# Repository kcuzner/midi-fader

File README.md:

# Simple MIDI Fader

By Kevin Cuzner

## Project Status

 * PCB complete and working (with an additional load added to reduce regulator noise)
 * Firmware feature-complete and mostly working
   * Emulates as HID and USB-MIDI devices
   * Not tested on Windows yet
 * Case OpenSCAD in progress
 * Configuration host software in progress

## Featureset

 * Two 60mm analog fader inputs
 * USB Audio Class interface, aiming for driverless on Windows 7 and 10
 * Driverless HID interface for configuration
   * It might be trivially simple to echo the fader status in the HID reports...

## Main Component Options

 * Faders (note that they have different footprints and different levers):
   * Expensive faders ($4.74, very light movement force): PTB6053-2010APB103-ND
   * Cheap faders ($1.73): PTA6043-2015CPB103-ND
 * Microcontrollers:
   * 497-17354-1-ND: STM32F070F6P6, $1.48, 32K flash, 6K RAM, 20-TSSOP.
     * No CRS, external XTAL required.
   * 497-15099-ND: STM32F070CBT6, $2.52, 128K flash, 16K RAM, 48-LQFP
     * No CRS, exteranl XTAL required.
   * 497-17344-ND: STM32042F6P6, $2.25, 32K flash, 6K RAM, 20-TSSOP.
     * Has a CRS
     * 24.6mA with all peripherals and HSI48 enabled
 * 609-4052-1-ND: Micro-USB, $0.76
 * 455-1790-1-ND: JST-SH header for programming, $0.63
 * Power supply solution:
   * MCP1603T-330I/OSCT-ND: Cheap buck regulator, but not too cheap. $1.01,
     TSOT-23
     * Noise issues at low currents (leaves PWM mode and skips pulses).
   * 576-4764-1-ND: MIC5504 buck regulator, $0.11, SOT23-5.
     * At a 100mA load, the case will heat 42.6C. Not over the top, but really
       quite hot.
     * We could do this AND the buck regulator, but just have this for the
       analog.

## Notes

### Notes about the logical MIDI protocol

 * MIDI has two types of bytes STATUS and DATA.
 * A STATUS byte has its MSB set
 * A DATA byte has its MSB cleared (hence why there are only ever 0 to 127 data
   values)
 * Usually, the lower nybble of the STATUS byte is a channel number (there are
   16 channels).
 * The number of data bytes to follow varies by which STATUS byte preceded them.
 * Interesting STATUS commands (upper nybble shown) for this project:
   * 0xB: Control Change. Followed by a controller number (1 data byte) and a
     controller value (1 data byte). Although there are possibly 127 controller
     numbers, numbers 120-127 are reserved for "Channel Mode Messages". Several
     of these are commonly used.
   * 0xE: Pitch Bend. Followed by two DATA bytes encoding a 14-bit value, LSB
     first. 0x2000 is center.
 * https://www.cs.cmu.edu/~music/cmsip/readings/MIDI%20tutorial%20for%20programmers.html
 * https://www.midi.org/specifications-old/item/table-1-summary-of-midi-message

### Notes about USB and MIDI

 * Windows XP and above seem to support USB MIDI except Elements.
   * "Elements" are things that process MIDI
   * "Jacks" are supported, and they are exactly what they sound like. This will
     implement a Jack.
   * Elements and Jacks are "Entities"
 * http://www.usb.org/developers/docs/devclass_docs/midi10.pdf

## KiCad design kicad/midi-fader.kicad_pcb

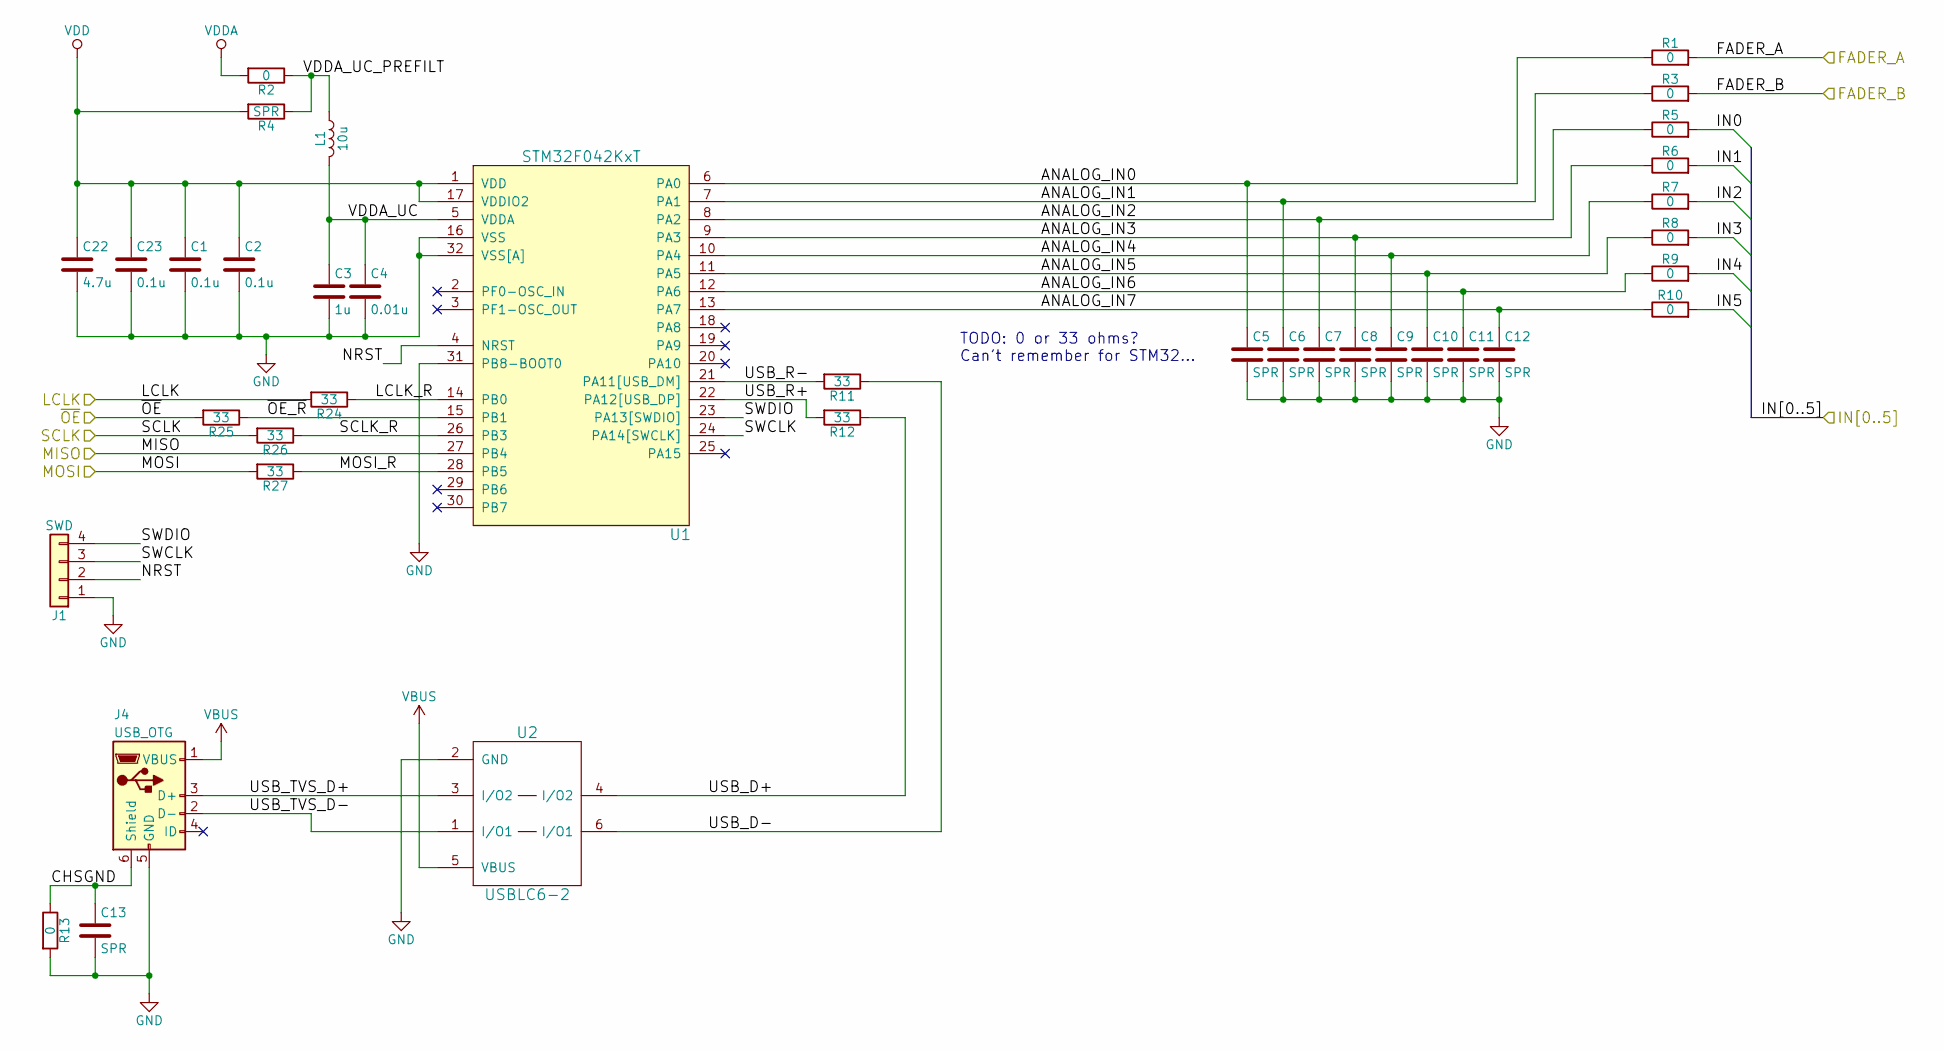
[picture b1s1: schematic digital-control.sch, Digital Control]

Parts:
C1, C2, C23: 0.1u; C_0402; Part No. 1276-1043-1-ND
C3: 1u; C_0603; Part No. 1276-1182-1-ND
C4: 0.01u; C_0402; Part No. 399-1038-1-ND
C5, C6, C7, C8, C9, C10, C11, C12, C13: SPR; C_0402
C22: 4.7u; C_0805; Part No. 1276-6464-1-ND
J1: SWD; JST-SH-4; Part No. 455-1790-1-ND
J4: USB_OTG; AMP-10104110-USB; Part No. 609-4052-1-ND
L1: 10u; R_0805; Part No. 587-2045-1-ND
R1, R2, R3, R5, R6, R7, R8, R9, R10, R13: 0; R_0402
R4: SPR; R_0402
R11, R12, R24, R25, R26, R27: 33; R_0402
U1: STM32F042KxT; LQFP-32_7x7mm_Pitch0.8mm; Part No. 497-14647-ND
U2: USBLC6-2; SOT-666; Part No. 497-5026-1-ND

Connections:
/Digital Control/ANALOG_IN0: C5.1, R1.1, U1.6 (PA0)
/Digital Control/ANALOG_IN1: C6.1, R3.1, U1.7 (PA1)
/Digital Control/ANALOG_IN2: C7.1, R5.1, U1.8 (PA2)
/Digital Control/ANALOG_IN3: C8.1, R6.1, U1.9 (PA3)
/Digital Control/ANALOG_IN4: C9.1, R7.1, U1.10 (PA4)
/Digital Control/ANALOG_IN5: C10.1, R8.1, U1.11 (PA5)
/Digital Control/ANALOG_IN6: C11.1, R9.1, U1.12 (PA6)
/Digital Control/ANALOG_IN7: C12.1, R10.1, U1.13 (PA7)
/Digital Control/CHSGND: C13.1, J4.6 (Shield), R13.1
/Digital Control/FADER_A: R1.2; also elsewhere on the board
/Digital Control/FADER_B: R3.2; also elsewhere on the board
/Digital Control/IN0: R5.2; also elsewhere on the board
/Digital Control/IN1: R6.2; also elsewhere on the board
/Digital Control/IN2: R7.2; also elsewhere on the board
/Digital Control/IN3: R8.2; also elsewhere on the board
/Digital Control/IN4: R9.2; also elsewhere on the board
/Digital Control/IN5: R10.2; also elsewhere on the board
/Digital Control/LCLK: R24.2; also elsewhere on the board
/Digital Control/LCLK_R: R24.1, U1.14 (PB0)
/Digital Control/MISO: U1.27 (PB4); also elsewhere on the board
/Digital Control/MOSI: R27.2; also elsewhere on the board
/Digital Control/MOSI_R: R27.1, U1.28 (PB5)
/Digital Control/NRST: J1.2, U1.4 (NRST)
/Digital Control/SCLK: R26.2; also elsewhere on the board
/Digital Control/SCLK_R: R26.1, U1.26 (PB3)
/Digital Control/SWCLK: J1.3, U1.24 (PA14[SWCLK])
/Digital Control/SWDIO: J1.4, U1.23 (PA13[SWDIO])
/Digital Control/USB_D+: R12.1, U2.4 (I/O2)
/Digital Control/USB_D-: R11.1, U2.6 (I/O1)
/Digital Control/USB_R+: R12.2, U1.22 (PA12[USB_DP])
/Digital Control/USB_R-: R11.2, U1.21 (PA11[USB_DM])
/Digital Control/USB_TVS_D+: J4.3 (D+), U2.3 (I/O2)
/Digital Control/USB_TVS_D-: J4.2 (D-), U2.1 (I/O1)
/Digital Control/VDDA_UC: C3.1, C4.1, L1.2, U1.5 (VDDA)
/Digital Control/VDDA_UC_PREFILT: L1.1, R2.1, R4.1
/Digital Control/~OE: R25.2; also elsewhere on the board
/Digital Control/~OE_R: R25.1, U1.15 (PB1)
GND: C1.2, C2.2, C3.2, C4.2, C5.2, C6.2, C7.2, C8.2, C9.2, C10.2, C11.2, C12.2, C13.2, C22.2, C23.2, J1.1, J4.5 (GND), R13.2, U1.16 (VSS), U1.31 (PB8-BOOT0), U1.32 (VSS[A]), U2.2 (GND); also elsewhere on the board
VBUS: J4.1 (VBUS), U2.5 (VBUS); also elsewhere on the board
VDD: C1.1, C2.1, C22.1, C23.1, R4.2, U1.1 (VDD), U1.17 (VDDIO2); also elsewhere on the board
VDDA: R2.2; also elsewhere on the board

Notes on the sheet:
TODO: 0 or 33 ohms? Can't remember for STM32...

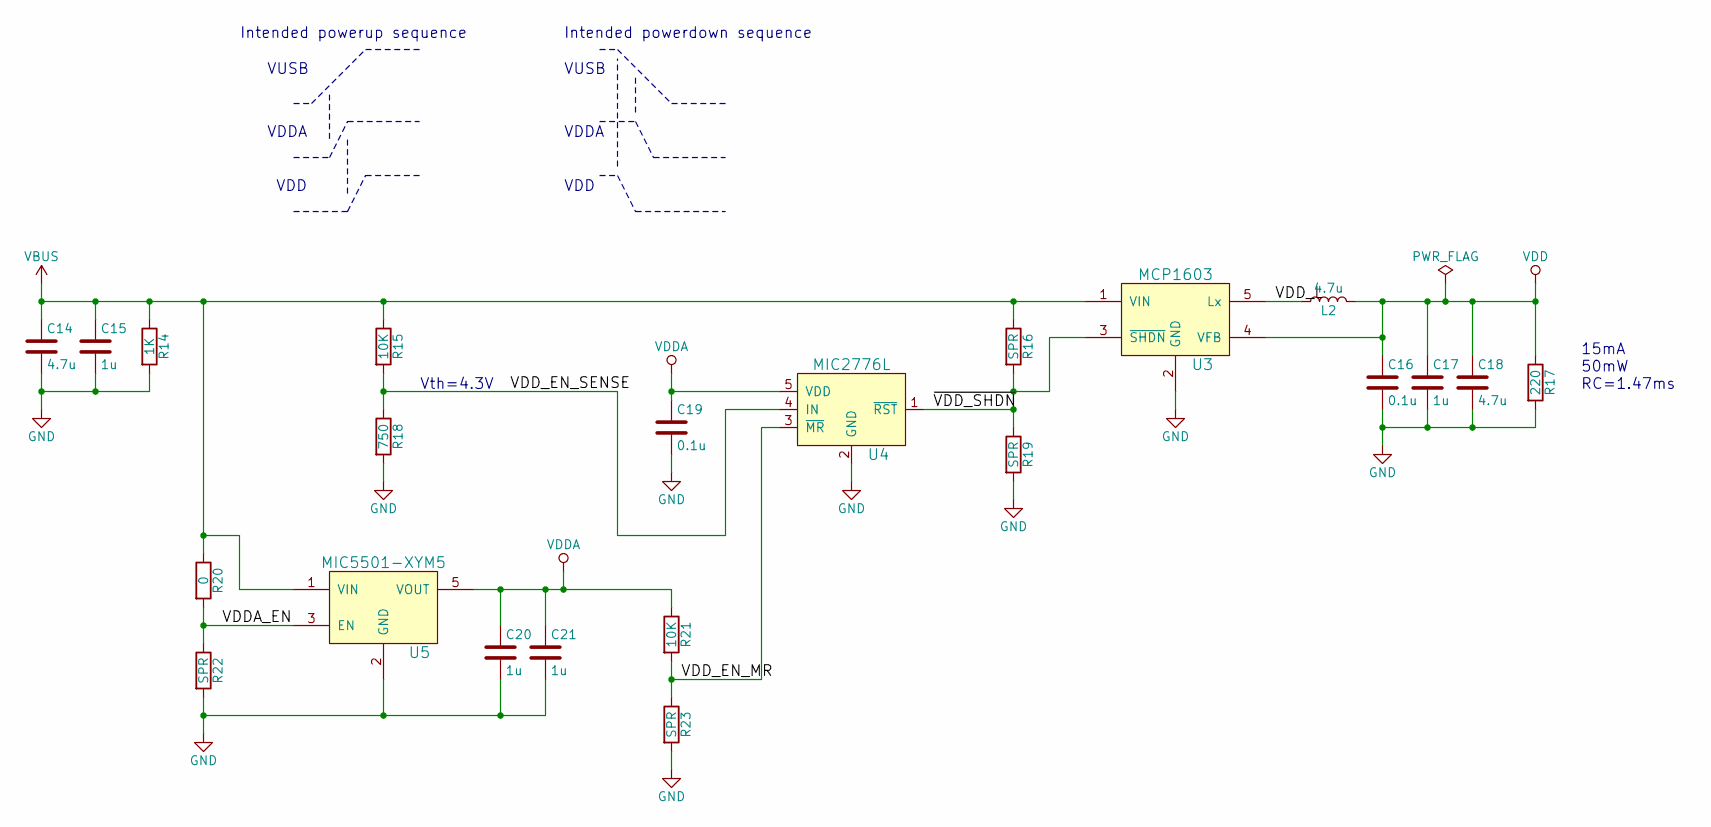
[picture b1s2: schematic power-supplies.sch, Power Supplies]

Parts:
C14, C18: 4.7u; C_0805; Part No. 1276-6464-1-ND
C15, C17, C20, C21: 1u; C_0603; Part No. 1276-1182-1-ND
C16, C19: 0.1u; C_0402; Part No. 1276-1043-1-ND
L2: 4.7u; Wurth_TPC_3816; Part No. 732-1008-1-ND
R14: 1K; R_0805
R15, R21: 10K; R_0402
R16, R19, R22, R23: SPR; R_0402
R17: 220; R_1206
R18: 750; R_0402
R20: 0; R_0402
U3: MCP1603; TSOT-23-5; Part No. MCP1603T-330I/OSCT-ND
U4: MIC2776L; SOT-23-5; Part No. 576-2686-1-ND
U5: MIC5501-XYM5; SOT-23-5; Part No. 576-4764-1-ND

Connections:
/Power Supplies/VDDA_EN: R20.2, R22.1, U5.3 (EN)
/Power Supplies/VDD_EN_MR: R21.2, R23.1, U4.3 (~MR)
/Power Supplies/VDD_EN_SENSE: R15.2, R18.1, U4.4 (IN)
/Power Supplies/VDD_L: L2.1, U3.5 (Lx)
/Power Supplies/~VDD_SHDN: R16.2, R19.1, U3.3 (~SHDN), U4.1 (~RST)
GND: C14.2, C15.2, C16.2, C17.2, C18.2, C19.2, C20.2, C21.2, R14.2, R17.2, R18.2, R19.2, R22.2, R23.2, U3.2 (GND), U4.2 (GND), U5.2 (GND); also elsewhere on the board
VBUS: C14.1, C15.1, R14.1, R15.1, R16.1, R20.1, U3.1 (VIN), U5.1 (VIN); also elsewhere on the board
VDD: C16.1, C17.1, C18.1, L2.2, R17.1, U3.4 (VFB); also elsewhere on the board
VDDA: C19.1, C20.1, C21.1, R21.1, U4.5 (VDD), U5.5 (VOUT); also elsewhere on the board

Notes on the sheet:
Intended powerup sequence
VUSB
VDDA
VDD
Intended powerdown sequence
15mA 50mW RC=1.47ms
Vth=4.3V

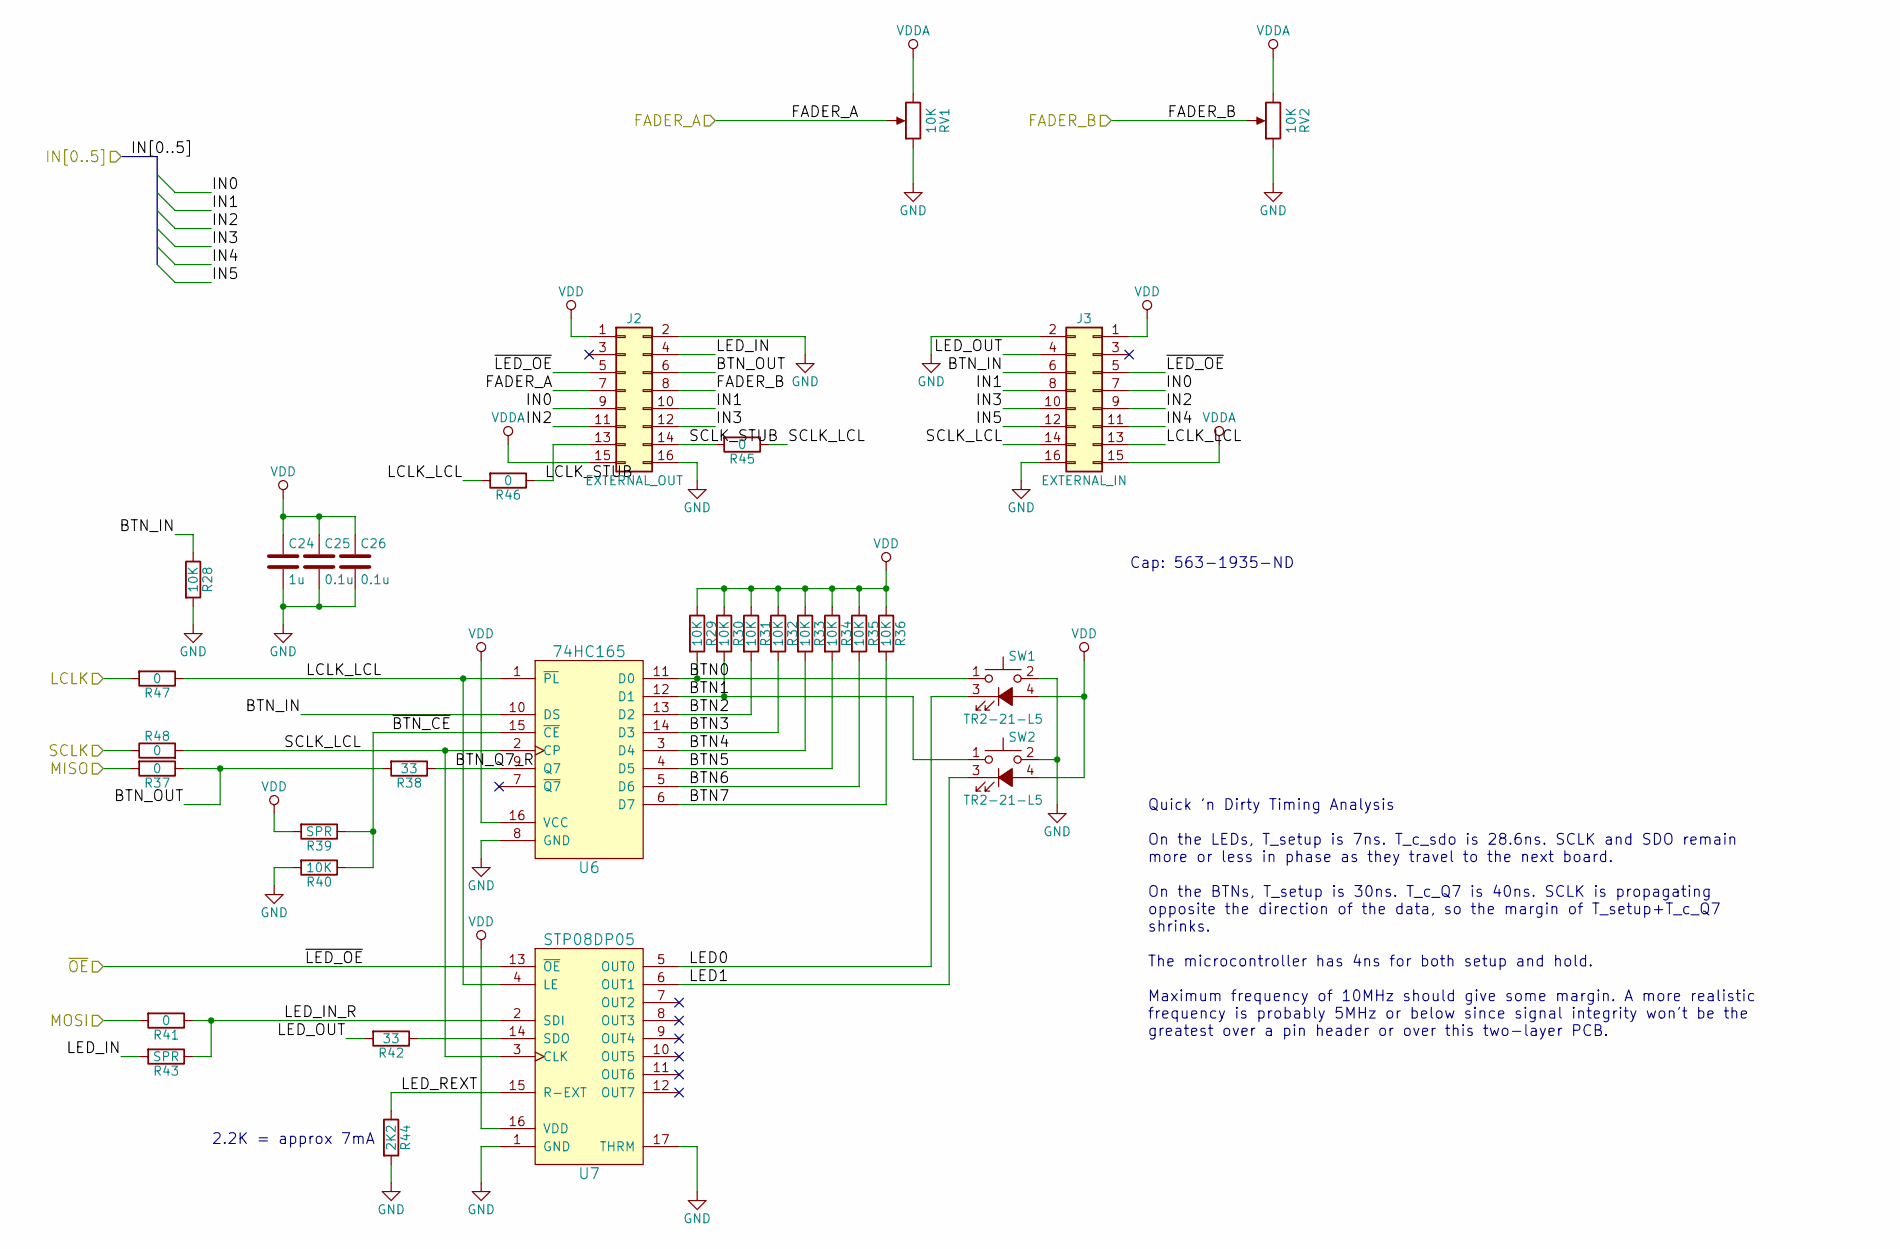
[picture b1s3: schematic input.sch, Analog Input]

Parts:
C24: 1u; C_0603; Part No. 1276-1182-1-ND
C25, C26: 0.1u; C_0402; Part No. 1276-1043-1-ND
J2: EXTERNAL_OUT; Pin_Header_Angled_2x08_Pitch2.54mm; Part No. 609-3346-ND
J3: EXTERNAL_IN; Socket_Strip_Angled_2x08_Pitch2.54mm; Part No. S5561-ND
R28, R29, R30, R31, R32, R33, R34, R35, R36, R40: 10K; R_0402
R37, R41, R45, R46, R47, R48: 0; R_0402
R38, R42: 33; R_0402
R39, R43: SPR; R_0402
R44: 2K2; R_0402
RV1, RV2: 10K; BOURNS_PTA60X3; Part No. PTA6043-2015CPB103-ND
SW1, SW2: TR2-21-L5; Nidec_Copal_TR2; Part No. 563-1933-ND
U6: 74HC165; TSSOP-16_4.4x5mm_Pitch0.65mm; Part No. 1727-4295-1-ND
U7: STP08DP05; HTSSOP-16-1EP_4.4x5mm_Pitch0.65mm_ThermalVias_HandSolder; Part No. 497-6119-1-ND

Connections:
/Digital Control/FADER_A: J2.7, RV1.2; also elsewhere on the board
/Digital Control/FADER_B: J2.8, RV2.2; also elsewhere on the board
/Digital Control/IN0: J2.9, J3.7; also elsewhere on the board
/Digital Control/IN1: J2.10, J3.8; also elsewhere on the board
/Digital Control/IN2: J2.11, J3.9; also elsewhere on the board
/Digital Control/IN3: J2.12, J3.10; also elsewhere on the board
/Digital Control/IN4: J3.11; also elsewhere on the board
/Digital Control/IN5: J3.12; also elsewhere on the board
/Digital Control/LCLK: R47.2; also elsewhere on the board
/Digital Control/MISO: R37.2; also elsewhere on the board
/Digital Control/MOSI: R41.2; also elsewhere on the board
/Digital Control/SCLK: R48.1; also elsewhere on the board
/Digital Control/~OE: J2.5, J3.5, U7.13 (~OE); also elsewhere on the board
/Input/BTN0: R29.2, SW1.1, U6.11 (D0)
/Input/BTN1: R30.2, SW2.1, U6.12 (D1)
/Input/BTN2: R31.2, U6.13 (D2)
/Input/BTN3: R32.2, U6.14 (D3)
/Input/BTN4: R33.2, U6.3 (D4)
/Input/BTN5: R34.2, U6.4 (D5)
/Input/BTN6: R35.2, U6.5 (D6)
/Input/BTN7: R36.2, U6.6 (D7)
/Input/BTN_IN: J3.6, R28.1, U6.10 (DS)
/Input/BTN_OUT: J2.6, R37.1, R38.2
/Input/BTN_Q7_R: R38.1, U6.9 (Q7)
/Input/LCLK_LCL: J3.13, R46.2, R47.1, U6.1 (~PL), U7.4 (LE)
/Input/LCLK_STUB: J2.13, R46.1
/Input/LED0: SW1.3 (K), U7.5 (OUT0)
/Input/LED1: SW2.3 (K), U7.6 (OUT1)
/Input/LED_IN: J2.4, R43.2
/Input/LED_IN_R: R41.1, R43.1, U7.2 (SDI)
/Input/LED_OUT: J3.4, R42.2
/Input/LED_REXT: R44.1, U7.15 (R-EXT)
/Input/SCLK_LCL: J3.14, R45.1, R48.2, U6.2 (CP), U7.3 (CLK)
/Input/SCLK_STUB: J2.14, R45.2
/Input/~BTN_CE: R39.1, R40.1, U6.15 (~CE)
GND: C24.2, C25.2, C26.2, J2.2, J2.16, J3.2, J3.16, R28.2, R40.2, R44.2, RV1.1, RV2.1, SW1.2, SW2.2, U6.8 (GND), U7.1 (GND), U7.17 (THRM); also elsewhere on the board
unnamed: R42.1, U7.14 (SDO)
VDD: C24.1, C25.1, C26.1, J2.1, J3.1, R29.1, R30.1, R31.1, R32.1, R33.1, R34.1, R35.1, R36.1, R39.2, SW1.4 (A), SW2.4 (A), U6.16 (VCC), U7.16 (VDD); also elsewhere on the board
VDDA: J2.15, J3.15, RV1.3, RV2.3; also elsewhere on the board

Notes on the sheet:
2.2K = approx 7mA
Quick 'n Dirty Timing Analysis On the LEDs, T_setup is 7ns. T_c_sdo is 28.6ns. SCLK and SDO remain more or less in phase as they travel to the next board. On the BTNs, T_setup is 30ns. T_c_Q7 is 40ns. SCLK is propagating opposite the direction of the data, so the margin of T_setup+T_c_Q7 shrinks. T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
Cap: 563-1935-ND

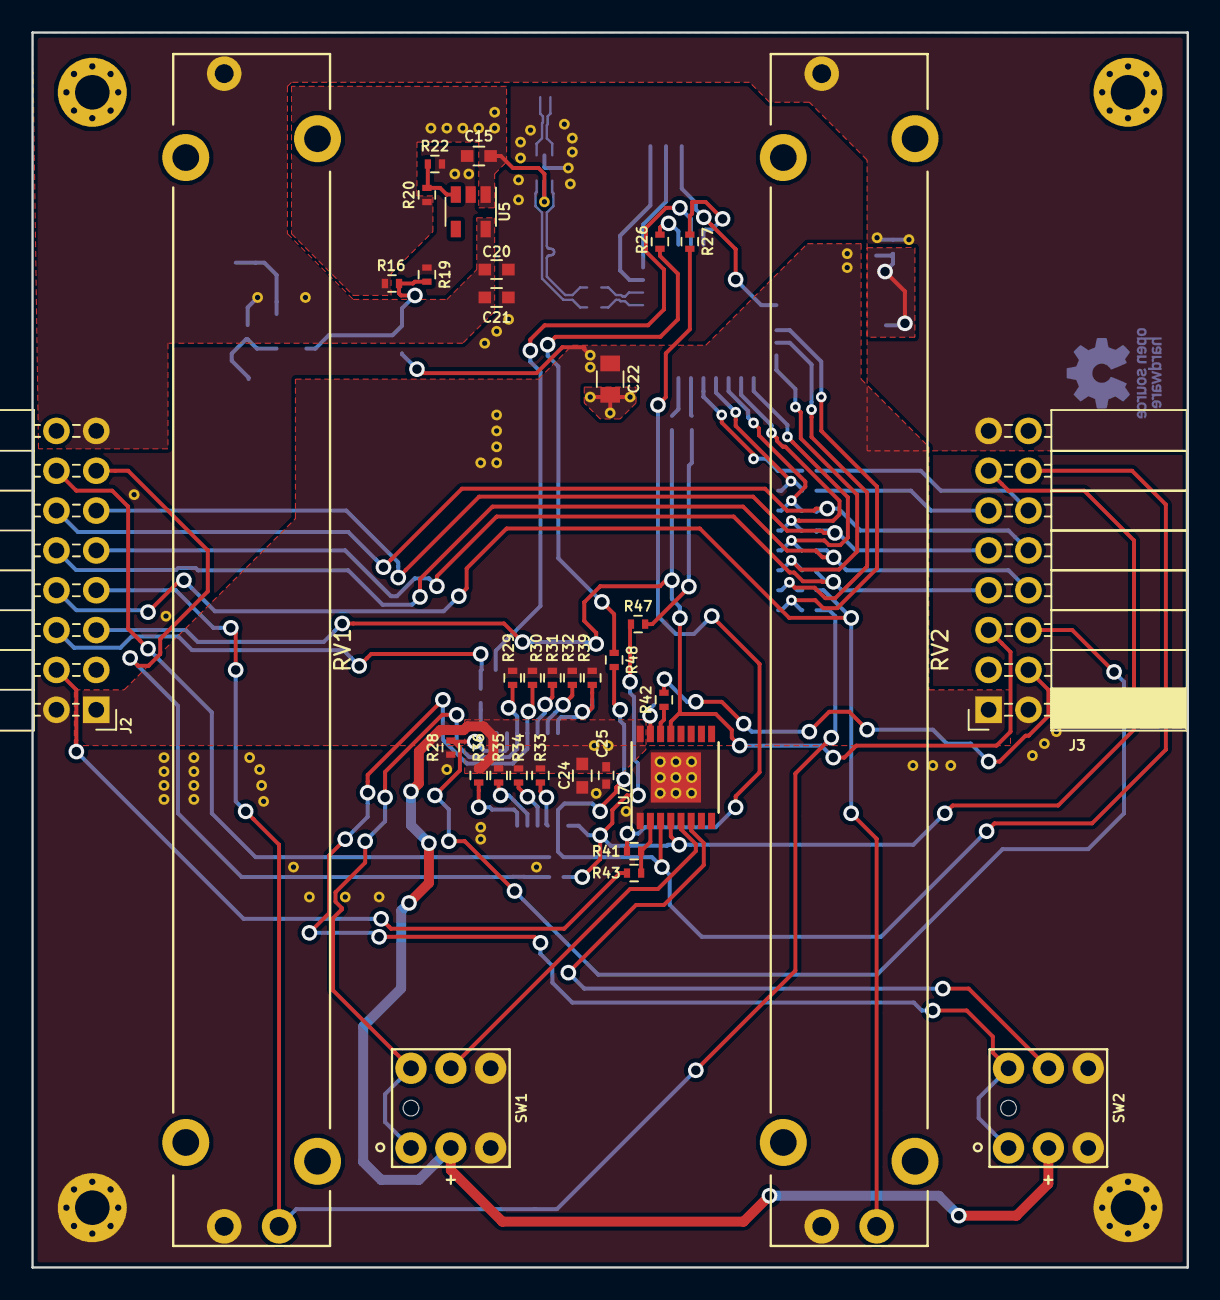
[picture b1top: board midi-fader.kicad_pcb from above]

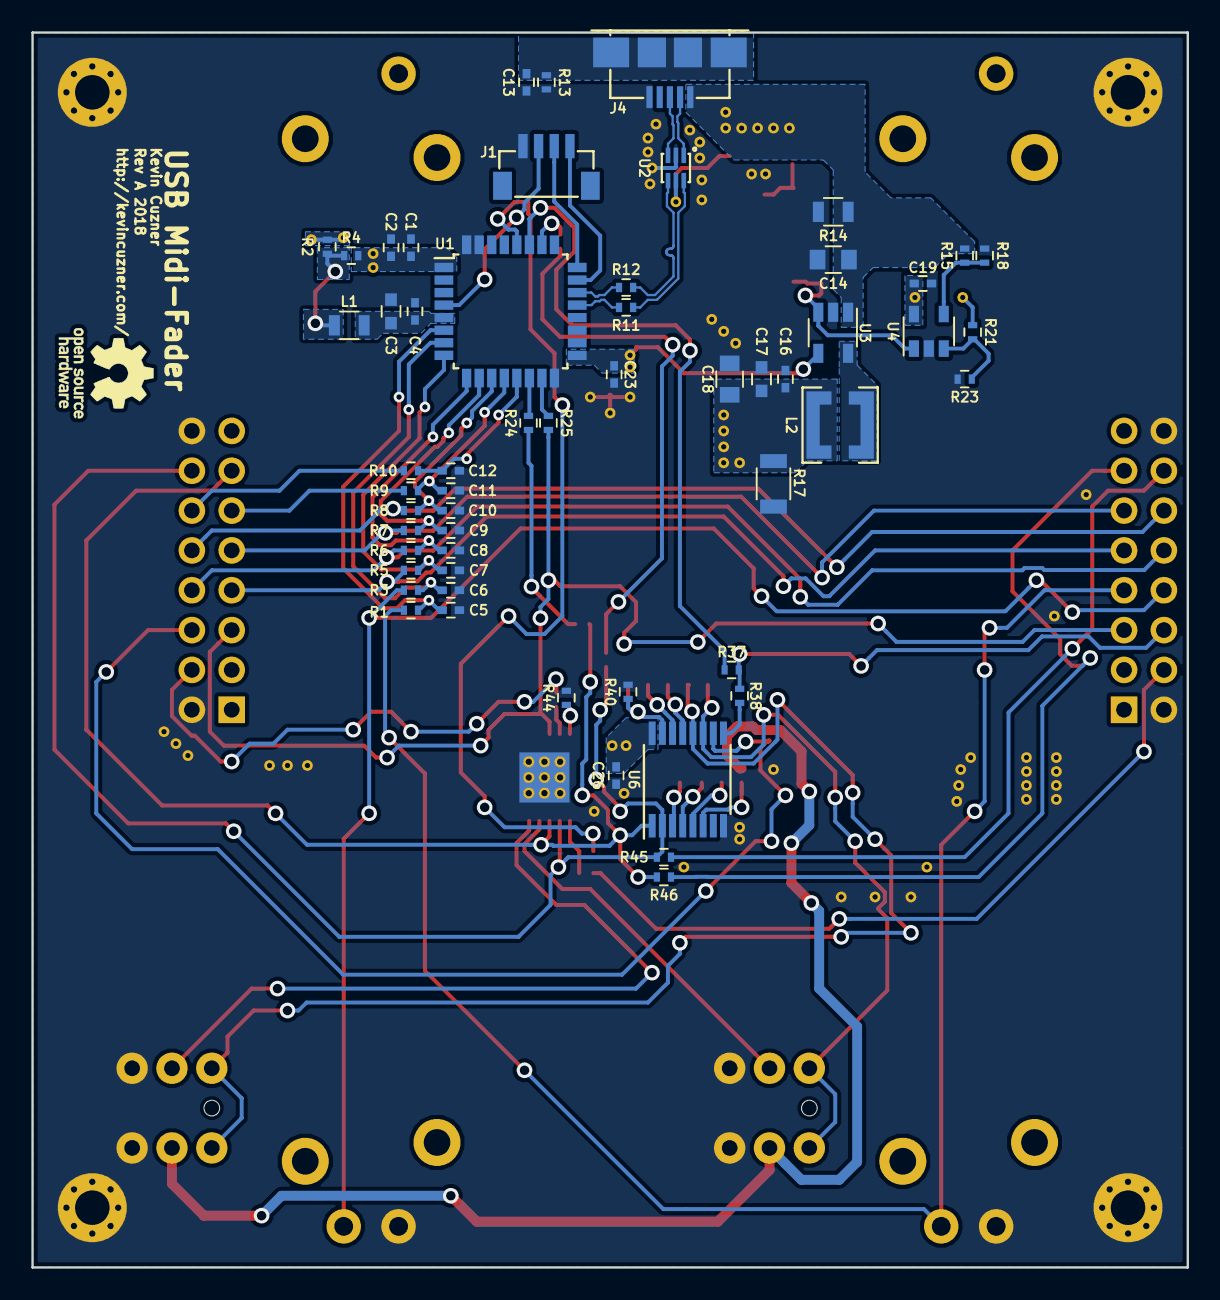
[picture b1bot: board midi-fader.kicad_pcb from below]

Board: 2 copper layers, 73.7 x 78.7 mm, 91 parts (56 on the bottom side), 69 nets.

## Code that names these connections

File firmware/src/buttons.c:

/**
 * USB Midi-Fader
 *
 * Buttons and LEDs
 *
 * Kevin Cuzner
 */

#include "buttons.h"

#include "stm32f0xx.h"
#include "systick.h"

/**
 * This uses the SPI peripheral to operate the shift registers that attach to
 * the buttons and LEDs on each midi-fader board.
 *
 * There can be up to four shift register pairs attached to one controller
 * board. The last shift register pair is noted by being all zeros when no
 * buttons are pressed. The number of channels in the system is determined by
 * how many of those bytes are non-zero. This number can grow and shrink
 * dynamically, even though we don't explicitly support hot-plugging of the
 * additional fader modules (in fact, I think it might cause weird behavior in
 * this module when they are being plugged in).
 */

/**
 * Receive buffer for the button status
 *
 * Buttons are clocked MSB first, so the 1st byte is this board and the last
 * byte is the farthest board.
 */
static volatile uint8_t buttons_status[4];
/**
 * Transmit buffer for the LED status
 *
 * LEDs are clocked MSB first, so the last byte is this board and the 1st byte
 * is the farthest board (opposite the buttons).
 */
static volatile uint8_t leds_status[4];

/**
 * Flag set to true when a transfer is ongoing
 */
static uint8_t transfer_ongoing = 0;

/**
 * Begins a DMA-driven transfer on the SPI if one isn't already ongoing.
 *
 * The DMA channel must be configured in advance
 *
 * This method should not be called reentrantly..
 */
static void buttons_begin_transfer(void)
{
    if (transfer_ongoing)
        return;
    // this variable is only set to 1 inside this method, which is not called
    // reentrantly.
    transfer_ongoing = 1;

    // Workaround for bad wiring: De-assert OE#, bring LCLK high.
    //
    // This allows the input shift register to give us good data, at the
    // expense of the LED register outputting everything as it sees it come
    // in from the master (hence deasserting OE#). To counteract the dimming
    // effect, the transfer is only initiated periodically rather than right
    // after the previous one finishes.
    //
    // Note that OE will be latched by the LEDs on the falling edge of the
    // first clock cycle, even though LCLK will be latched on the rising edge.
    GPIOB->BSRR = GPIO_BSRR_BS_0 | GPIO_BSRR_BS_1;

    // Set up the DMA transfer sizes
    DMA1_Channel2->CNDTR = sizeof(buttons_status);
    DMA1_Channel3->CNDTR = sizeof(leds_status);

    // See section 25.8.9 in the reference manual for this procedure
    // Step 1: Enable RX DMAEN
    SPI1->CR2 |= SPI_CR2_RXDMAEN;
    // Step 2: Enable DMA Streams
    DMA1_Channel2->CCR |= DMA_CCR_EN;
    DMA1_Channel3->CCR |= DMA_CCR_EN;
    // Step 3: Enable TX DMAEN
    SPI1->CR2 |= SPI_CR2_TXDMAEN;
    // Step 4: Start the transfer
    SPI1->CR1 |= SPI_CR1_SPE;
}

/**
 * Concludes a DMA-driven transfer on the SPI
 *
 * This should only be called once the receive transfer (DMA_Channel3)
 * is completed.
 *
 * Also pulses the LCLK both to prepare the buttons for the next transfer
 * and to display the LED values from this transfer
 *
 * This method should not be called reentrantly.
 */
static void buttons_end_transfer(void)
{
    // See section 25.8.9 in the reference manual for this procedure
    // Step 1: Disable the DMA streams
    DMA1_Channel3->CCR &= ~DMA_CCR_EN;
    // Step 2: Follow the SPI disable procedure
    // Step 2.1: Wait for the transmit fifo to be empty
    while (SPI1->SR & SPI_SR_FTLVL_Msk) { }
    // Step 2.2: Wait for busy to clear
    while (SPI1->SR & SPI_SR_BSY) { }
    // Step 2.3: Disable the SPI
    SPI1->CR1 &= ~SPI_CR1_SPE;
    // Step 2.4: Wait for the receive buffer to clear
    while (SPI1->SR & SPI_SR_FRLVL_Msk) { }
    //TODO: I suspect that I should keep RX enabled until this point, just in case
    DMA1_Channel2->CCR &= ~DMA_CCR_EN;
    // Step 3: Clear the DMAEN bits
    SPI1->CR2 &= ~(SPI_CR2_RXDMAEN | SPI_CR2_TXDMAEN);

    // Workaround for bad wiring: Assert OE#, bring LCLK low.
    //
    // This is the reverse of the workaround during the begin transfer phase.
    // It also latches the next batch of data.
    GPIOB->BSRR = GPIO_BSRR_BR_0 | GPIO_BSRR_BR_1;

    // Perform one extra clock cycle.
    //
    // The rising edge latches LCLK and the falling edge latches OE#.
    //
    // Hopefully this doesn't wreak to much havoc with the buttons. The PL#
    // input is asynchronous and it is deasserted just before the first clock
    // cycle the next transaction, so the buttons *should* have the most
    // recent value. Everything looks right when tested with only one shift
    // register, so I don't know if this actually works.
    GPIOB->BSRR = GPIO_BSRR_BR_3;
    GPIOB->MODER ^= GPIO_MODER_MODER3_1 | GPIO_MODER_MODER3_0;
    GPIOB->BSRR = GPIO_BSRR_BS_3;
    GPIOB->BSRR = GPIO_BSRR_BR_3;
    GPIOB->MODER ^= GPIO_MODER_MODER3_1 | GPIO_MODER_MODER3_0;

    // This is only reset in this one place, and this is not called reentrantly.
    transfer_ongoing = 0;
}

void buttons_init(void)
{
    // Enable SPI and GPIOB
    RCC->APB2ENR |= RCC_APB2ENR_SPI1EN;
    RCC->AHBENR |= RCC_AHBENR_GPIOBEN;

    // Enable DMA
    RCC->AHBENR |= RCC_AHBENR_DMA1EN;

    // PB0, PB1, PB3, PB4, and PB5 are the button/led pins
    GPIOB->MODER &= ~(GPIO_MODER_MODER0_Msk | GPIO_MODER_MODER1_Msk |
            GPIO_MODER_MODER3_Msk | GPIO_MODER_MODER4_Msk |
            GPIO_MODER_MODER5_Msk);

    // Configure latch clock and OE pins
    //
    // LCLK: PB0 (starts low)
    // OE#: PB1 (starts high)
    GPIOB->BSRR = GPIO_BSRR_BR_0 | GPIO_BSRR_BS_1;
    GPIOB->OTYPER &= ~(GPIO_OTYPER_OT_0 | GPIO_OTYPER_OT_1);
    GPIOB->OSPEEDR |= GPIO_OSPEEDR_OSPEEDR0_0 | GPIO_OSPEEDR_OSPEEDR0_1 |
        GPIO_OSPEEDR_OSPEEDR1_0 | GPIO_OSPEEDR_OSPEEDR1_1;
    GPIOB->MODER |= GPIO_MODER_MODER0_0 | GPIO_MODER_MODER1_0;

    // Configure SPI pins
    //
    // AF0 of PB3, PB4, and PB5
    GPIOB->MODER |= GPIO_MODER_MODER3_1 | GPIO_MODER_MODER4_1 |
        GPIO_MODER_MODER5_1;
    GPIOB->AFR[0] &= ~(GPIO_AFRL_AFSEL3_Msk | GPIO_AFRL_AFSEL4_Msk |
            GPIO_AFRL_AFSEL5_Msk);
    // We enable the internal pulldowns on all of these pins
    GPIOB->PUPDR |= GPIO_PUPDR_PUPDR3_1 | GPIO_PUPDR_PUPDR4_1 |
        GPIO_PUPDR_PUPDR5_1;

    // Configure the SPI
    //
    // MSB first, fastest speed possible, no slave select.
    SPI1->CR1 = SPI_CR1_SSM | SPI_CR1_SSI | SPI_CR1_MSTR;
    SPI1->CR2 = SPI_CR2_FRXTH | SPI_CR2_DS_0 | SPI_CR2_DS_1 | SPI_CR2_DS_2;

    //DMA Channel 2 handles SPI1_RX
    DMA1_Channel2->CPAR = (uint32_t)(&SPI1->DR);
    DMA1_Channel2->CMAR = (uint32_t)(buttons_status);
    // Enable the transfer complete interrupt, since this completes last
    // once we've sent everything.
    DMA1_Channel2->CCR = DMA_CCR_MINC | DMA_CCR_TEIE | DMA_CCR_TCIE;

    //DMA Channel 3 handles SPI1_TX
    DMA1_Channel3->CPAR = (uint32_t)(&SPI1->DR);
    DMA1_Channel3->CMAR = (uint32_t)(leds_status);
    // Only enable the transfer error interrupt
    DMA1_Channel3->CCR = DMA_CCR_MINC | DMA_CCR_DIR | DMA_CCR_TEIE;

    NVIC_EnableIRQ(DMA1_Channel2_3_IRQn);

    // Subscribe to system ticks. Every tick we begin a transfer.
    systick_subscribe(&buttons_begin_transfer);
}

uint8_t buttons_get_count(void)
{
    uint8_t i;
    for (i = 0; i < 4; i++)
    {
        if (!buttons_status[i])
            break;
    }
    // buttons always come in pairs
    return i * 2;
}

uint8_t buttons_read(void)
{
    uint8_t compressed = 0;
    for (uint8_t i = 0; i < sizeof(buttons_status); i++)
    {
        compressed >>= 2;
        // 1st button is the LSB of the byte
        compressed |= ((~buttons_status[i]) & 0x3) << 6;
    }
    return compressed;
}

void buttons_write_leds(uint8_t leds)
{
    for (uint8_t i = 0; i < sizeof(leds_status); i++)
    {
        // last button is index 0, 1st button is the last index
        leds_status[(sizeof(leds_status)-1)-i] = leds & 0x3;
        leds >>= 2;
    }
}

void SPI1_IRQHandler(void)
{
}

static uint32_t transfers = 0;

void DMA1_Channel2_3_IRQHandler(void)
{
    if (DMA1->ISR & DMA_ISR_TEIF2)
    {
        // Channel 2 DMA error, just clear it for now
        DMA1->IFCR = DMA_IFCR_CTEIF2;
    }
    if (DMA1->ISR & DMA_ISR_TCIF2)
    {
        transfers++;
        // Channel 2 transfer complete. We have finished transacting all the
        // bytes in the buffer.
        buttons_end_transfer();
    }
    if (DMA1->ISR & DMA_ISR_TEIF3)
    {
        // Channel 3 DMA error, just clear it for now
        DMA1->IFCR = DMA_IFCR_CTEIF3;
    }

    DMA1->IFCR = DMA_IFCR_CGIF2 | DMA_IFCR_CGIF3;
}

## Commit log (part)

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2018-07-05 Finished initial part selection, built footprints
    I'm not sure about my footprint selection for the expansion headers,
    even though it is just a 0.1" header I want to be fairly exact about the
    length the pins stick out and how close the female header is to the
    edge, so that I can get a good distance between the two boards.
2018-07-05 Added 3D models and made initial sizing placement
    I haven't compensated for the thickness of the case walls yet so that
    may need some adjustment. The objective is to have the sliders all
    equidistant when they are plugged in a row.
2018-07-05 Changed microcontroller to 32-LQFP variety
2018-07-06 Initial routing complete
2018-07-06 Added corner grounded mounting holes
    At the moment I plan on actually attaching the cover using the M2 screw
    holes on the sliders themselves, but this seems like a good backup
    option to have.
2018-07-06 Saved global dimension settings
2018-07-08 Created shift register circuitry and imported footprints
    I think 5MHz to 10MHz is the theoretical maximum of this circuit. Actual
    frequency will probably be around 5MHz or somewhat less given the signal
    integrity issues on a 2-layer board with this many plane breaks.
    Created footprints for button and HTSSOP
    The HTSSOP footprint is special because I plan to hand solder, so I
    added excessive thermal vias and a bare pad on the backside.
2018-07-13 Layout completed, first pass
2018-07-14 Added stub-removal resistors on clock lines, started cleaning silkscreen
2018-07-14 Finished refdes tweaks, added OSHW logo and license
2018-07-14 Moved sense location of VDD
2018-07-14 Fixed NPTH on the sliders
    Those are not supposed to be non-plated. Whoops.
2018-07-14 Adding Rev A gerbers
2018-07-25 Added initial makefile, cmsis stuff, and bare main.c
2018-07-25 Added hardfault debug helper
2018-07-26 Fixed the initial stack vector
2018-07-26 Added dependency generation for c files
2018-07-28 Added USB application layer to begin support for multiple interfaces
    The application layer implements command fallthrough for the setup
    requests and maybe someday should implement discrimination on when a
    particular hook for sent/received is called depending on if the endpoint
    belongs to the interface.
2018-07-28 Added readme for firmware
2018-08-04 Changed descriptor format drastically, scaffolded the parser
2018-08-06 Created scaffold for endpoints and raw descriptors
2018-08-09 Added initial source code generation
    Although our language descriptor is malformed (but maybe not too
    malformed...I think it might still meet sped), the system appears to be
    working.
2018-08-11 Replaced descriptors with generated ones
2018-08-19 Fixed USB transmit logic
    Also added some usb debug logging and made the descriptors static
2018-08-19 Fixed issues with endpoint assignment and status
    The descriptorgen needed to be changed so that it talks in terms of
    endpoint numbers, not addresses.
    The usb_endpoint_setup method also had an issue where it would keep
    endpoints disabled, even though they were set up. Those endpoints now
    NAK instead, which I believe is the correct behavior. At least now
    ardour doesn't flood my log with -32 errors when it tries to read the
2018-08-21 Added initial sending of an event
    It fails after the 3rd buffer is filled. The processor hard faults.
2018-08-22 Simplified buffer to resolve the hard fault, fixed reset issue
    The device gets occasional resets, but the midi interface did not reset
    its internal buffer. It will now reset its buffer every time it is
    (re)configured.
2018-08-23 Added initial stab at protocol definition
2018-08-25 Added initial storage section and generator at end of flash
    The XML file contains the configuration and the python script generates
    the appropriate structures. The linker script reserves a section of the
    flash for this special storage.
2018-08-25 Changed parameter and size to 16 bits, reduced required storage
2018-08-27 Added untested flash writing and storage migration methods
2018-08-29 Added magic number to mark that a storage section is ready
2018-08-31 Fixed issue with usb descriptor generator comment extraction
    It was pulling out comments that didn't belong to it. I now check that
    it contains at least one <descriptor> tag.
2018-08-31 Fixed storage and configuration implementation, added verbose errors
    There were many tiny bugs with the storage implementation, especially
    with writing and migration. Enough of them are fixed that I can now
    write a value 512 times (which migrates at least twice) and have no
    issues.
    Yeah error is a bad name...
2018-09-06 Upgraded schematic to Kicad 5
2018-09-06 Added getter for the latest fader data
2018-09-08 Added initial DMA-driven shift registers
    There is a big problem: I made a mistake with LE and PL#. Apparently
    when PL# is low, the shift register always outputs high. However,
    whenever LE is high it will continually load the LEDs, so the user would
    see weird LED patterns.
    I think I can work around this by briefly turning off the LEDs. The
    transactions take like 20us to complete.
2018-09-10 Fixed issues with the STP08DP05 and SPI
    Apparently all signals are synchronous. This isn't immediately obvious
    from the datasheet, but the Table 9 does attempt to clearly show it.
    The various issues here were mainly fixed by enabling pulldowns (since
    the SPI Hi-Z's everything when disabled) and temporarily changing the
    SCLK I/O back to a regular output briefly to create an extra clock pulse
    when performing the latching operation.
2018-09-14 Fixed issues with the read btns and write leds methods
2018-09-15 Changed Midi logic to use a lossy ring buffer and ZLPs
    This should prevent stale data from being queued somewhat, so long as
    the device only sends data when necessary.
2018-09-15 Fixed a rather subtle mistake with the midi queue
    It wasn't properly asking if the queue was empty. It would only
    partially flush the queue and only rarely actually fully flush it.
    This caused buffers to be transmitted one after the other, which it
    turns out actually bogs down the processor significantly. Stuff would
    still respond, but very delayed.
2018-09-15 Added storage abstraction to the configuration layer
    This should keep us from needing to put the storage.xml-based magic
    variable names everywhere. Instead, we can call functions which will
    read the storage for us.
2018-09-15 Updated the readme WIP flags
2018-09-19 Added fantastically cheap averaging to the fader
    I can just keep getting data, so if I just sum every Nth element of
    the data array I can very easily get an average. Pleasantly surprised.
2018-09-19 Added resending of the entire state if it's been a while
2018-09-19 Moved configurator to the firmware scripts
    I will not be using it as host software, even though it is. It is a test
    tool for firmware development really.
2018-09-19 Changed configurator to use names and fixed storage bug
    Just a tiny bug with reading the configuration, it wouldn't have
    affected the operation of the device.
2018-09-20 Split things for the bootloader into a common directory
    Also split out the NVM methods into their own thing since the bootloader
    will need to use these directly.
    One possible issue here is that our HID reports could vary between
    binaries. I may need to make a separate required usb_hid_desc.c in the
    bootloader and firmware that contains only the HID report. Although, for
    now I intend for them to use the same reports.
2018-09-20 Added initial bootloader from the led-watch project, non-working
2018-09-22 Modified the bootloader to actually compile
    It now uses the storage system instead of EEPROM. The VTOR emulation is
    still a work in progress.
2018-09-26 Added VTOR emulation to the bootloader
2018-09-26 Fixed bootloader vector table alignment problem
2018-09-27 Changed bootloader dispatcher to use reserved RAM instead of the PC
    If an interrupt interrupted another one at just the right time it would
    see that it was inside the bootloader...and immediately jump to the
    bootloader code instead of the user app code. The reserved RAM approach
    is far simpler.
2018-09-29 Added initial bootloader python programmer script
    I needed to add an explicit erase command since the erase size and the
    program size are not the same on the STM32F0xx.
    I added the initial implementation of the midi-fader resetting into the
    bootloader, but I have not yet been successful in getting the actual
    firmware to run. There is a bug right now with the script where it can't
    handle dis-contiguous hex files for some reason.
2018-09-29 Fixed the case where blocks are non-contiguous
    If the address of the new segment is after the address of the current
    segment, but still within the page, we get to pad.
2018-09-30 Fixed a bug with the hid endpoints, the bootloader now works
    There is still some unreliablility when aborting the bootloader and then
    changing the device back into bootloader mode. However, for development
    this is acceptable.
2018-11-13 Updated license to full text of Apache 2.0
2018-12-05 Updated firmware readme for additional dependencies
    Apparently nosys.specs comes from newlib...
2018-12-22 Fixed USB descriptor string length problem
2018-12-22 Updated storage to new defaults that fix pitch bend problems
2018-12-25 Changed debug trace for USB to be more verbose
2019-02-16 Downgraded USB version to avoid requesting the device qualifier
    There is most definitely a problem involving stalls, so the fewer
    planned stalls the better I think.
2019-02-16 Expanded USB logging considerably so that every event is logged
    The result of this experiment is that there is definitely a problem with
    the control transfer state machine. It frequently stalls on transactions
    that should be considered valid.
2019-02-21 Added logging of every ISTR value to the USB
2019-09-09 Adding residual kicad file
2019-09-09 Upgraded dependencies
2019-09-09 Changed readback of parameter collections to be macro-based
    Got rid of a lot of repetitive code, but now I have some very very ugly
    types.
2019-09-09 Implemented reading complete device configuration
2019-09-09 Adding quick host readme
2019-09-09 Added the firmware status command
2019-09-09 Completed state machine for finding the device and improved docs
2019-09-09 Started scaffolding with imgui to see if it will work
    I think this GUI is probably the one I'm going to have the most success
    with with rust. GUI stuff still isn't quite there yet IMO.
2019-09-09 Changed device to use raw libc calls, started making futures
2019-09-09 Started moving the device abstraction to be Evented
    I'm attempting to implemente asynchronous reads/writes.
2019-09-09 Changed out error_chain for failure
    Apparently error_chain is deprecated, but the real reason for this
    change is the fact that error_chain is !Send. The failure crate is far
    simpler and will be Send if the underlying types are Send.
2019-09-09 Refactored GUI to use From traits on the various states
2019-09-09 Added concept of updatable parameter types
2019-09-09 Fixed reads/writes; futures now work
2019-09-09 WIP adding windows support
2019-09-09 Added initial device abstraction for linux
2019-09-09 Added dual-mpsc based message passing; almost compiles
2019-09-09 Added animation to finding and waiting screens
2019-09-09 Added future for performing a complete midi fader command
2019-09-09 Added gui methods for showing and updating the control values
